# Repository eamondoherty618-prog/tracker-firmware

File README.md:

# 123 Mobile Track

Firmware, recovery tools, and deployment helpers for the tracker hardware
behind `123 Mobile Track`.

Current firmware: `v0.11.1`

## Start here

- [Build one tracker](docs/build-one-tracker.md)
- [Project map](docs/project-map.md)
- [Hardware wiring](docs/hardware-wiring.md)
- [Deployment guide](DEPLOYMENT.md)

## What is in this repo

| Path | What it is |
|---|---|
| `src/`, `include/`, `platformio.ini` | Tracker firmware. |
| `flash_new_tracker.sh` | Flash a brand-new board over USB and log its ID. |
| `make_sd_card.sh` | Build a field-recovery microSD card. |
| `deploy_firmware.sh` | Build and publish an OTA firmware release. |
| `fleet_inventory.csv` | Flash log for boards that have been provisioned. |
| `hardware/obd_tracker_carrier_v1/` | KiCad carrier-board files, BOM, placement file, and mechanical references. |
| `docs/` | Plain-English build guide, diagrams, wiring, and system overview. |

## Quick build and flash

```sh
pio run
pio run -t upload
./flash_new_tracker.sh
./make_sd_card.sh /Volumes/YOURCARD
```

## How the system fits together

1. The tracker boots on a `LilyGo T-SIM7000G`.
2. It reads GPS and optional add-ons like CAN/OBD2 or the impact sensor.
3. It sends telemetry to `123mobiletrack.com`.
4. The app and dashboard show the live vehicle state.
5. OTA releases are published from this repo and pulled by the trackers on
   their next check-in.

If you need the wiring details or the install order, start with the build guide
above.

## Repo hygiene

Tracked files should be firmware, deployment scripts, docs, and hardware source
files. Generated outputs, local KiCad session files, zip packages, telemetry
logs, PlatformIO builds, and unrelated shop/design files are ignored.

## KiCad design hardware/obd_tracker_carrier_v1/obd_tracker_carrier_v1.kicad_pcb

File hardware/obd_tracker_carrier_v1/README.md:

# OBD Tracker Carrier Board v1

This package is a v1 KiCad-oriented carrier design for the proven LilyGo
T-SIM7000G + CAN + ADXL375 vehicle tracker architecture.

## Architecture Decision

Use **Option A** for v1: a carrier board for the proven LilyGo T-SIM7000G module.
The LilyGo already integrates the ESP32-WROVER, SIM7000G, USB flashing, SIM,
GNSS/LTE RF, battery charging, and antennas. Keeping it as a replaceable module
cuts RF/layout risk and small-batch cost. A fully native ESP32/SIM7000G board is
the right v2 only after fleet field data proves the enclosure, power section,
and harness approach.

## Board Geometry

- Board: **88.0 x 40.0 mm**, 1.6 mm FR-4. The KiCad source is a 2-layer v1 scaffold; a 4-layer production finalization is recommended for better EMI and thermal margin.
- Mounting holes: M2.5 clearance, 2.7 mm drill, 5.6 mm copper keepout.
- Hole centers:
  - H1: (4.0, 4.0) mm
  - H2: (84.0, 4.0) mm
  - H3: (84.0, 36.0) mm
  - H4: (4.0, 36.0) mm
- LilyGo module envelope: 66.0 x 27.0 mm at lower-left coordinate (18.0, 6.5) mm.
- Optional bottom 18650 holder envelope: 76.0 x 21.0 mm at lower-left coordinate (8.0, 9.5) mm.

The DXF contains the exact outline, hole centers, LilyGo envelope, and 18650
alternate footprint. The STEP file is a simplified board envelope for enclosure
blocking; use the DXF for exact hole cutouts.

## Functional Nets

- OBD2 input: J1 pin 1 = OBD16 +12V, pin 2 = OBD4 GND, pin 3 = OBD6 CAN-H, pin 4 = OBD14 CAN-L.
- CAN transceiver: TJA1051T/3 or equivalent, TXD -> GPIO32, RXD -> GPIO33, VCC = 5V, VIO = 3.3V.
- ADXL375: SDA -> GPIO21, SCL -> GPIO22, INT1 -> GPIO34, CS high, SDO low for address 0x53.
- Vehicle ADC: protected VIN through 100k/20k divider and 100nF filter to GPIO35.
- Battery ADC: VBAT through 1M/1M divider and 100nF filter to GPIO36.
- Status LED: GPIO23 active high, optional.
- Reserved LilyGo pins: GPIO26/27 modem UART and GPIO2/13/14/15 SD remain unconnected.

## Power Section

The v1 power path is:

`OBD +12V -> F1 resettable fuse -> D2 SMBJ33A TVS -> D1 5A reverse Schottky -> TPS54360 60V buck -> +5V`

The +5V rail feeds the LilyGo VIN/charger path and the 5V CAN transceiver. The
carrier uses the LilyGo's onboard 3.3V regulator and charge circuit. Battery
support is either J2 JST-PH LiPo or BT1 bottom-side 18650 holder, populated per
build, routed to the LilyGo battery/charger pins.

## Build Notes

- DNP R10/JP1 for normal vehicle installs. Only populate 120 ohm termination for bench setups or isolated test harnesses.
- L2 CAN common-mode choke is optional. Populate a CAN choke or 0-ohm bypass links after EMI testing.
- The generated routing scaffold uses bottom-layer orthogonal routes for bottom-side SMD circuitry, including CAN, TPS54360 support nets, ADXL375 I2C/INT, and ADC dividers.
- Use short, twisted OBD harness conductors for CAN-H/CAN-L and keep the harness shield/return strategy consistent with the enclosure.
- Place the ADXL375 side of the board against a rigid standoff area; avoid foam tape directly under the accelerometer if impact fidelity matters.
- Verify the exact LilyGo T-SIM7000G board revision and header geometry before fab. This reference uses the user-supplied 66 x 27 mm target envelope.
- For the lowest-height build, DNP BT1 and use a flat LiPo pouch via J2.

## Files

- `obd_tracker_carrier_v1.kicad_pro` - KiCad project settings and net classes.
- `obd_tracker_carrier_v1.kicad_pcb` - PCB outline, footprints, placement, pad nets, and baseline routing scaffold.
- `obd_tracker_carrier_v1.kicad_sch` - top-level schematic notes in KiCad format.
- `obd_tracker_carrier_v1_legacy.sch` - legacy KiCad schematic notes fallback.
- `bom/obd_tracker_carrier_v1_bom.csv` - BOM with suggested MPNs and LCSC/JLCPCB fields to verify at order time.
- `bom/obd_tracker_carrier_v1_netlist.csv` - readable netlist.
- `fab/obd_tracker_carrier_v1_placement.csv` - placement/mechanical coordinate table.
- `fab/obd_tracker_carrier_v1_stats.rpt` - KiCad-generated board statistics, created by the validation/export pass.
- `fab/obd_tracker_carrier_v1_erc.rpt` - KiCad schematic ERC report, created by the validation/export pass.
- `fab/VALIDATION.md` - validation commands and DRC limitation note.
- `mechanical/obd_tracker_carrier_v1_outline.dxf` - exact 2D board outline/hole/envelope DXF.
- `mechanical/obd_tracker_carrier_v1_board_reference.step` - simplified board envelope STEP.
- `mechanical/obd_tracker_carrier_v1_kicad_board.step` - KiCad-generated board-only STEP, created by the validation/export pass.
- `mechanical/kicad_dxf/` - KiCad-generated DXF exports for Edge.Cuts, Dwgs.User, and B.Fab.

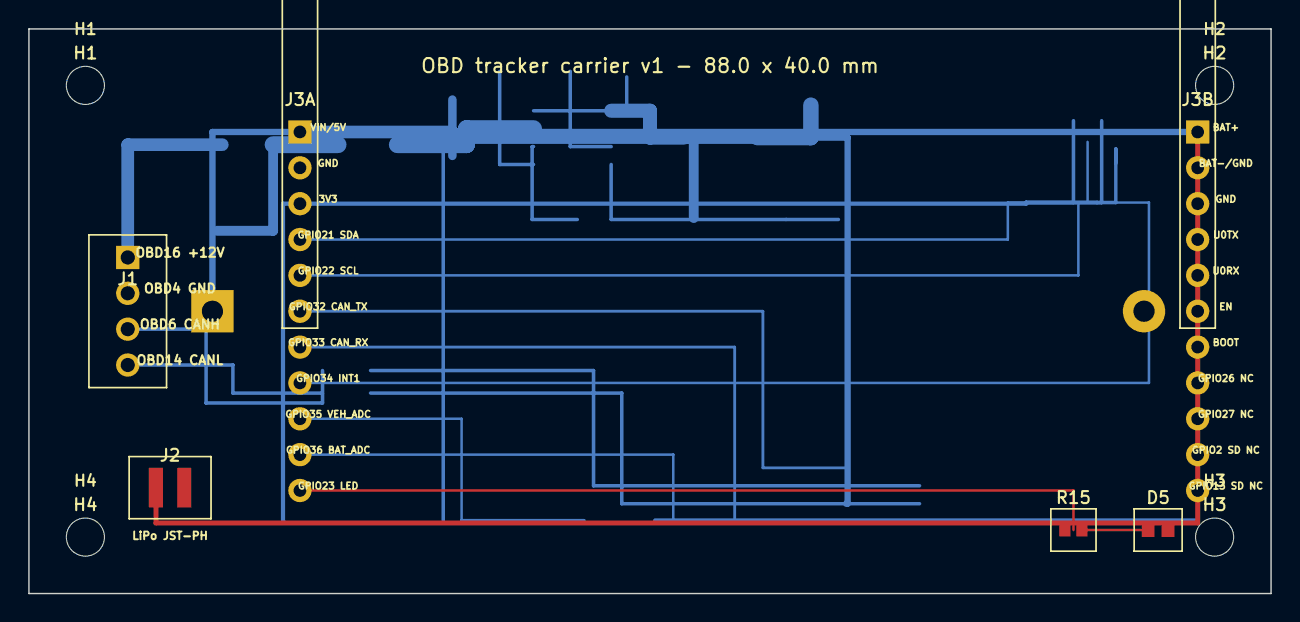
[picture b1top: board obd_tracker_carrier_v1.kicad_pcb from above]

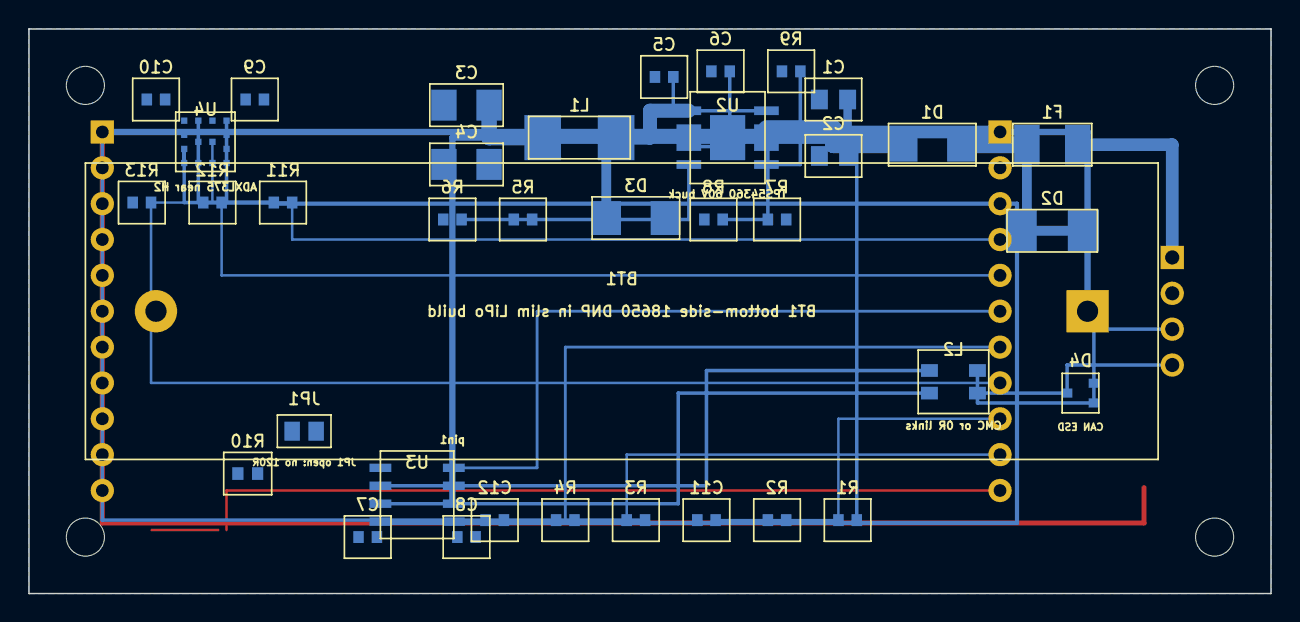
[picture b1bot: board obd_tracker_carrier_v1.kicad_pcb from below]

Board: 2 copper layers, 88.0 x 40.0 mm, 47 parts (37 on the bottom side), 27 nets.

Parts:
BT1: Single 18650 holder alternate footprint; BatteryHolder_18650
C1, C2: 10uF 50V input cap; SMD_2Pad
C3, C4: 47uF 10V output cap; SMD_2Pad
C5: 100nF bootstrap; SMD_2Pad
C6: Compensation cap placeholder; SMD_2Pad
C7: 100nF CAN VCC; SMD_2Pad
C8: 100nF CAN VIO; SMD_2Pad
C9: 100nF accel decoupling; SMD_2Pad
C10: 1uF accel decoupling; SMD_2Pad
C11: 100nF vehicle ADC filter; SMD_2Pad
C12: 100nF battery ADC filter; SMD_2Pad
D1: B560C/SS56 reverse Schottky; SMD_2Pad
D2: SMBJ33A load-dump TVS; SMD_2Pad
D3: B560C buck catch diode; SMD_2Pad
D4: CAN ESD protector, SOT-23; SOT-23
D5: Green status LED; SMD_2Pad
F1: 2A resettable fuse, 1812; SMD_2Pad
H1, H2, H3, H4: M2.5 mounting hole; MountingHole_M2.5
J1: OBD2 harness 12V/GND/CANH/CANL; Harness_4P_2.54
J2: JST-PH-2 LiPo, populate instead of BT1; JST_PH_S2B-PH-SM4-TB
J3A, J3B: T-SIM7000G low profile header rail; TSIM_Header_Rail
JP1: Optional CAN termination solder jumper, open by d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; SolderJumper_2_Open
L1: 15uH shielded inductor >=4A; SMD_2Pad
L2: CAN common-mode choke DNP/0R bypass; CommonModeChoke_CAN
R1: 100k vehicle ADC top; SMD_2Pad
R2: 20.0k vehicle ADC bottom; SMD_2Pad
R3: 1.0M battery ADC top; SMD_2Pad
R4: 1.0M battery ADC bottom; SMD_2Pad
R5: 52.3k 1% FB top; SMD_2Pad
R6: 10.0k 1% FB bottom; SMD_2Pad
R7: 200k EN top; SMD_2Pad
R8: 49.9k EN bottom; SMD_2Pad
R9: 200k RT; SMD_2Pad
R10: 120R CAN termination DNP; SMD_2Pad
R11: 4.7k I2C SDA pull-up; SMD_2Pad
R12: 4.7k I2C SCL pull-up; SMD_2Pad
R13: 100k INT1 pulldown; SMD_2Pad
R15: 1k LED series; SMD_2Pad
U2: TPS54360DDAR 12V-to-5V buck; TI_SO-PowerPAD-8
U3: TJA1051T/3 5V CAN transceiver; SOIC-8_3.9x4.9mm_P1.27mm
U4: ADXL375BCCZ-RL7; ADXL375_LGA-14

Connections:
+3V3: C8.1, C9.1, C10.1, J3A.3 (3V3), R11.2, R12.2, U3.5, U4.1, U4.3, U4.6, U4.7
+5V: C3.1, C4.1, C7.1, J3A.1 (VIN/5V), L1.2, R5.1, U3.3
ACCEL_INT1_GPIO34: J3A.8 (GPIO34 INT1), R13.1, U4.8
BUCK_BOOT: C5.1, U2.1
BUCK_COMP: C6.1, U2.6
BUCK_EN: R7.2, R8.1, U2.3
BUCK_FB: R5.2, R6.1, U2.5
BUCK_RT: R9.1, U2.4
BUCK_SW: C5.2, D3.2, L1.1, U2.8
CANH: JP1.1, L2.3, U3.7
CANH_OBD: D4.1 (CANH), J1.3 (OBD6 CANH), L2.1
CANL: L2.4, R10.2, U3.6
CANL_OBD: D4.3 (CANL), J1.4 (OBD14 CANL), L2.2
CAN_RX_GPIO33: J3A.7 (GPIO33 CAN_RX), U3.4
CAN_TERM_H: JP1.2, R10.1
CAN_TX_GPIO32: J3A.6 (GPIO32 CAN_TX), U3.1
GND: BT1.2 (BAT-), C1.2, C2.2, C3.2, C4.2, C6.2, C7.2, C8.2, C9.2, C10.2, C11.2, C12.2, D2.2, D3.1, D4.2 (GND), D5.2, J1.2 (OBD4 GND), J2.2 (BAT-), J3A.2 (GND), J3B.2 (BAT-/GND), J3B.3 (GND), R2.2, R4.2, R6.2, R8.2, R9.2, R13.2, U2.7, U2.9, U3.2, U3.8, U4.2, U4.4, U4.5, U4.10, U4.12
I2C_SCL_GPIO22: J3A.5 (GPIO22 SCL), R12.1, U4.14
I2C_SDA_GPIO21: J3A.4 (GPIO21 SDA), R11.1, U4.13
LED_A: D5.1, R15.2
STATUS_LED_GPIO23: J3A.11 (GPIO23 LED), R15.1
VBAT: BT1.1 (BAT+), J2.1 (BAT+), J3B.1 (BAT+), R3.1
VBAT_SENSE_GPIO36: C12.1, J3A.10 (GPIO36 BAT_ADC), R3.2, R4.1
VEH_SENSE_GPIO35: C11.1, J3A.9 (GPIO35 VEH_ADC), R1.2, R2.1
VIN_FUSED: D1.1, D2.1, F1.2
VIN_OBD: F1.1, J1.1 (OBD16 +12V)
VIN_PROT: C1.1, C2.1, D1.2, R1.1, R7.1, U2.2

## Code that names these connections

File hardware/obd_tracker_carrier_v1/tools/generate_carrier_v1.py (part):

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    "CANL_OBD",
    "CANH",
    "CANL",
    "CAN_TX_GPIO32",
    "CAN_RX_GPIO33",
    "I2C_SDA_GPIO21",
    "I2C_SCL_GPIO22",
    "ACCEL_INT1_GPIO34",
    "VEH_SENSE_GPIO35",
    "VBAT_SENSE_GPIO36",
    "STATUS_LED_GPIO23",
    "BOOT_DEBUG",
    "EN_DEBUG",
    "U0TX_DEBUG",
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        ("5", 1.5, -0.5, "GND", "GND"),
        ("6", 1.5, 0.5, "+3V3", "VS"),
        ("7", 1.5, 1.5, "+3V3", "CS_HIGH"),
        ("8", 0.5, 1.5, "ACCEL_INT1_GPIO34", "INT1"),
        ("9", -0.5, 1.5, None, "INT2_NC"),
        ("10", -1.5, 1.5, "GND", "GND"),
        ("11", -1.5, 0.5, None, "NC"),
        ("12", -1.5, -0.5, "GND", "SDO_LOW"),
        ("13", -0.5, 0, "I2C_SDA_GPIO21", "SDA"),
        ("14", 0.5, 0, "I2C_SCL_GPIO22", "SCL"),
    ]
    body = rect_body(4.2, 4.2, silk)
    for num, x, y, n, _ in pads:
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
def make_status_led() -> list[str]:
    return [
        make_2pad("R15", "1k LED series", (74.0, 35.5), "F.Cu", ("STATUS_LED_GPIO23", "LED_A"), size=(0.8, 0.9), pitch=1.2),
        make_2pad("D5", "Green status LED", (80.0, 35.5), "F.Cu", ("LED_A", "GND"), size=(0.9, 1.0), pitch=1.4),
    ]

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def make_can_esd() -> str:
    layer = "B.Cu"
    body = rect_body(2.6, 2.8, "B.SilkS")
    body.append(smd_pad("1", -0.95, 0.7, "CANH_OBD", layer, size=(0.75, 0.65), pinfunction="CANH"))
    body.append(smd_pad("2", -0.95, -0.7, "GND", layer, size=(0.75, 0.65), pinfunction="GND"))
    body.append(smd_pad("3", 0.95, 0, "CANL_OBD", layer, size=(0.75, 0.65), pinfunction="CANL"))
    body.append(fp_text("user", "CAN ESD", 0, 2.4, "B.SilkS", 0.5))
    return footprint("D4", "CAN ESD protector, SOT-23", (13.5, 25.8), layer, body, "Package_TO_SOT_SMD:SOT-23")

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        ("VIN/5V", "+5V"),
        ("GND", "GND"),
        ("3V3", "+3V3"),
        ("GPIO21 SDA", "I2C_SDA_GPIO21"),
        ("GPIO22 SCL", "I2C_SCL_GPIO22"),
        ("GPIO32 CAN_TX", "CAN_TX_GPIO32"),
        ("GPIO33 CAN_RX", "CAN_RX_GPIO33"),
        ("GPIO34 INT1", "ACCEL_INT1_GPIO34"),
        ("GPIO35 VEH_ADC", "VEH_SENSE_GPIO35"),
        ("GPIO36 BAT_ADC", "VBAT_SENSE_GPIO36"),
        ("GPIO23 LED", "STATUS_LED_GPIO23"),
    ]
    header_b = [
        ("BAT+", "VBAT"),
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                "TJA1051T/3 5V CAN transceiver",
                (60.5, 33.0),
                {
                    1: "CAN_TX_GPIO32",
                    2: "GND",
                    3: "+5V",
                    4: "CAN_RX_GPIO33",
                    5: "+3V3",
                    6: "CANL",
                    7: "CANH",
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            make_adxl375(),
            make_2pad("C9", "100nF accel decoupling", (72.0, 5.0), "B.Cu", ("+3V3", "GND"), size=(0.75, 0.85), pitch=1.3),
            make_2pad("C10", "1uF accel decoupling", (79.0, 5.0), "B.Cu", ("+3V3", "GND"), size=(0.75, 0.85), pitch=1.3),
            make_2pad("R11", "4.7k I2C SDA pull-up", (70.0, 12.3), "B.Cu", ("I2C_SDA_GPIO21", "+3V3"), size=(0.75, 0.85), pitch=1.3),
            make_2pad("R12", "4.7k I2C SCL pull-up", (75.0, 12.3), "B.Cu", ("I2C_SCL_GPIO22", "+3V3"), size=(0.75, 0.85), pitch=1.3),
            make_2pad("R13", "100k INT1 pulldown", (80.0, 12.3), "B.Cu", ("ACCEL_INT1_GPIO34", "GND"), size=(0.75, 0.85), pitch=1.3),
            make_2pad("R1", "100k vehicle ADC top", (30.0, 34.8), "B.Cu", ("VIN_PROT", "VEH_SENSE_GPIO35"), size=(0.75, 0.85), pitch=1.3),
            make_2pad("R2", "20.0k vehicle ADC bottom", (35.0, 34.8), "B.Cu", ("VEH_SENSE_GPIO35", "GND"), size=(0.75, 0.85), pitch=1.3),
            make_2pad("C11", "100nF vehicle ADC filter", (40.0, 34.8), "B.Cu", ("VEH_SENSE_GPIO35", "GND"), size=(0.75, 0.85), pitch=1.3),
            make_2pad("R3", "1.0M battery ADC top", (45.0, 34.8), "B.Cu", ("VBAT", "VBAT_SENSE_GPIO36"), size=(0.75, 0.85), pitch=1.3),
            make_2pad("R4", "1.0M battery ADC bottom", (50.0, 34.8), "B.Cu", ("VBAT_SENSE_GPIO36", "GND"), size=(0.75, 0.85), pitch=1.3),
            make_2pad("C12", "100nF battery ADC filter", (55.0, 34.8), "B.Cu", ("VBAT_SENSE_GPIO36", "GND"), size=(0.75, 0.85), pitch=1.3),
        ]
    )
    fps.extend(make_status_led())
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        ("canl_obd_choke", "CANL_OBD", 0.25, "B.Cu", [(14.45, 25.8), (20.8, 25.8)]),
        ("canh_bus", "CANH", 0.25, "B.Cu", [(24.2, 24.2), (40.0, 24.2), (40.0, 32.365), (63.1, 32.365)]),
        ("canl_bus", "CANL", 0.25, "B.Cu", [(24.2, 25.8), (42.0, 25.8), (42.0, 33.635), (63.1, 33.635)]),
        ("can_tx", "CAN_TX_GPIO32", 0.2, "B.Cu", [(19.2, 19.999), (52.0, 19.999), (52.0, 31.095), (57.9, 31.095)]),
        ("can_rx", "CAN_RX_GPIO33", 0.2, "B.Cu", [(19.2, 22.539), (50.0, 22.539), (50.0, 34.905), (57.9, 34.905)]),
        ("i2c_sda_pullup", "I2C_SDA_GPIO21", 0.18, "B.Cu", [(19.2, 14.919), (69.35, 14.919), (69.35, 12.3)]),
        ("i2c_sda_accel", "I2C_SDA_GPIO21", 0.18, "B.Cu", [(69.35, 12.3), (75.0, 12.3), (75.0, 8.0)]),
        ("i2c_scl_pullup", "I2C_SCL_GPIO22", 0.18, "B.Cu", [(19.2, 17.459), (74.35, 17.459), (74.35, 12.3)]),
        ("i2c_scl_accel", "I2C_SCL_GPIO22", 0.18, "B.Cu", [(74.35, 12.3), (76.0, 12.3), (76.0, 8.0)]),
        ("accel_int_pull", "ACCEL_INT1_GPIO34", 0.18, "B.Cu", [(19.2, 25.079), (79.35, 25.079), (79.35, 12.3)]),
        ("accel_int_u4", "ACCEL_INT1_GPIO34", 0.18, "B.Cu", [(79.35, 12.3), (76.0, 12.3), (76.0, 9.5)]),
        ("rail_3v3_pullups", "+3V3", 0.3, "B.Cu", [(19.2, 12.379), (70.65, 12.379), (70.65, 12.3), (75.65, 12.3)]),
        ("rail_3v3_accel_1", "+3V3", 0.25, "B.Cu", [(70.65, 12.3), (74.0, 12.3), (74.0, 6.5)]),
        ("rail_3v3_accel_3", "+3V3", 0.25, "B.Cu", [(75.65, 12.3), (76.0, 12.3), (76.0, 6.5)]),
        ("rail_3v3_accel_6_7", "+3V3", 0.25, "B.Cu", [(75.65, 12.3), (77.0, 12.3), (77.0, 8.5), (77.0, 9.5)]),
        ("rail_3v3_can_vio", "+3V3", 0.3, "B.Cu", [(19.2, 12.379), (18.0, 12.379), (18.0, 35.0), (63.1, 35.0), (63.1, 34.905)]),
        ("vehicle_adc", "VEH_SENSE_GPIO35", 0.18, "B.Cu", [(19.2, 27.619), (30.65, 27.619), (30.65, 34.8), (39.35, 34.8)]),
        ("battery_adc", "VBAT_SENSE_GPIO36", 0.18, "B.Cu", [(19.2, 30.159), (45.65, 30.159), (45.65, 34.8), (54.35, 34.8)]),
        ("vbat_jst_to_lilygo", "VBAT", 0.35, "F.Cu", [(9.0, 32.5), (9.0, 35.0), (82.8, 35.0), (82.8, 7.3)]),
        ("vbat_18650", "VBAT", 0.45, "B.Cu", [(13.0, 20.0), (13.0, 7.3), (82.8, 7.3)]),
        ("vbat_adc", "VBAT", 0.25, "B.Cu", [(82.8, 7.3), (82.8, 34.8), (44.35, 34.8)]),
        ("status_gpio", "STATUS_LED_GPIO23", 0.18, "F.Cu", [(19.2, 32.699), (74.0, 32.699), (74.0, 35.5)]),
        ("status_led", "LED_A", 0.18, "F.Cu", [(74.6, 35.5), (79.3, 35.5)]),
    ]
    out: list[str] = []
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        (18, 20, "OBD2 harness: pin16 +12V, pin4 GND, pin6 CAN-H, pin14 CAN-L"),
        (18, 34, "Input protection: F1 PTC -> SMBJ33A TVS -> B560C reverse Schottky -> VIN_PROT"),
        (18, 48, "Buck: TPS54360 60V class regulator, 5V/2A target, feeds LilyGo VIN and CAN VCC"),
        (18, 62, "CAN: TJA1051T/3, TX GPIO32, RX GPIO33, no 120R termination by default"),
        (18, 76, "ADXL375: I2C GPIO21/22, addr 0x53 via CS high and SDO low, INT1 GPIO34"),
        (18, 90, "ADC: vehicle VIN_PROT divider to GPIO35, battery divider to GPIO36"),
        (18, 104, "Battery: route LilyGo charge/BAT pins to JST-PH LiPo or alternate bottom 18650 holder"),
        (18, 118, "Keep LilyGo modem UART GPIO26/27 and SD GPIO2/13/14/15 unconnected"),
        (18, 136, "Open the PCB and CSV netlist for exact pad/net assignments; verify LilyGo board revision before fab."),
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Comp "Codex generated reference design"
$EndDescr
Text Notes 900 900 0 100 ~ 0
OBD2 pin16 +12V -> F1 PTC -> D2 SMBJ33A TVS -> D1 reverse Schottky -> VIN_PROT
Text Notes 900 1450 0 100 ~ 0
VIN_PROT -> TPS54360 60V buck -> +5V, 2A target. +5V feeds LilyGo VIN and TJA1051 VCC.
Text Notes 900 2000 0 100 ~ 0
TJA1051T/3: TXD=GPIO32, RXD=GPIO33, VIO=3V3, VCC=5V. No 120R termination unless JP1/R10 populated.
Text Notes 900 2550 0 100 ~ 0
ADXL375: SDA=GPIO21, SCL=GPIO22, INT1=GPIO34, CS tied high, SDO tied low for I2C address 0x53.
Text Notes 900 3100 0 100 ~ 0
GPIO35 senses protected vehicle input through 100k/20k RC divider. GPIO36 senses VBAT through 1M/1M RC divider.
Text Notes 900 3650 0 100 ~ 0
Battery build options: JST-PH LiPo OR bottom 18650 holder, populated per build. Both route to LilyGo BAT pins/charger.
Text Notes 900 4200 0 100 ~ 0
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
def make_bom_rows() -> list[dict[str, str]]:
    rows = [
        ("J1", "OBD2 harness connector, 4 pos locking or screw terminal", "Molex Micro-Fit 3.0 43045-0400 preferred; KF128-2.54-4P alt", "KF128 alt C474922; Micro-Fit verify/consign", "1", "Populate one connector style. Pin order: 12V, GND, CANH, CANL."),
        ("F1", "Resettable fuse, 1812, 30V, hold 2.0A", "LUTE 1812L200/30GRT", "C49326271", "1", "Place before TVS so reverse/transient faults are current-limited."),
        ("D1", "Reverse-polarity series Schottky, 5A, 60V", "GOODWORK SS56 or equivalent", "C2848693", "1", "Schottky v1 for simplicity. PFET ideal-diode option can replace after thermal testing."),
        ("D2", "Automotive input TVS, 600W, 33V standoff", "Jingdao SMBJ33A or automotive-qualified equivalent", "C353366", "1", "Choose working voltage above jump-start/normal operation and below buck abs-max clamp margin."),
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
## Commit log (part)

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2026-05-25 Initial project import
